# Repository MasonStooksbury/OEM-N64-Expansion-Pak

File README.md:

# OEM-N64-Expansion-Pak | KiCad 8.0

At long last! Here are the all the files you would need to create your own OEM Expansion Pak. All you would need to do is clone this repo, open the .kicad_pro file in KiCad, and you can poke around the files. [Here's a video of it working!](https://www.youtube.com/watch?v=sDxaTl5USwA)

I use this plugin in KiCad to make it super easy to order boards with all the correct settings: [https://www.pcbway.com/blog/News/PCBWay_Plug_In_for_KiCad_3ea6219c.html](https://www.pcbway.com/blog/News/PCBWay_Plug_In_for_KiCad_3ea6219c.html)

## Some things to note:

 - ***Unless you have a 4MB RAM chip, this board will not do you any good***. Most of the old stock you will find are 2MB chips. Don't fret, I have [another open source board](https://github.com/MasonStooksbury/Open-Source-N64-Expansion-Pak) that utilizes two of these chips so that you can make your own Expansion Pak. This one is just for historical reference. That being said, you can find instructions for ordering a board with the settings I use at PCBWay below in the "Making your own board" section if you happen to come across some 4MB modules, or you harvest them from a broken N64 (assuming you have the model with one 4MB chip as opposed to the ones with two 2MB chips)

 - The "ExpansionPak.pretty" folder is a library containing all the footprints needed for the project. Including the Edge Connector footprint created by Bigbass (check out more of his stuff here: [https://hachyderm.io/@bigbass](https://hachyderm.io/@bigbass) and here: [https://github.com/bigbass1997](https://github.com/bigbass1997/)). This saved me countless hours and pain, so a huge shoutout to him for allowing me to use it and release it

 - The schematic is probably not in an "official" format. But it's laid out in such a way that you can easily understand which pins on the Edge Connector are connected to which pins on the RAM chip. This was done on purpose as I feel it is a bit easier to understand for most people.

 - The pictured board and the render look different because I needed to change some things once I got the board. Namely, the corners were in the way of the original Expansion Pak mounting columns (if you look at an OEM one, they have cutouts). I also needed to modify the screw holes because they were too small.

Thank you so much to everyone who has followed along, commented, gave me feedback, and more. It's all very much appreciated and I'm excited to be able to give back. And another huge shoutout to Bigbass for allowing me to use their Edge Connector as it was a perfect fit and saved me countless revisions and lots of headache.

# Making your own board

## Installing necessary software, pulling the project, and uploading everything to PCBWay
 - First, download KiCad [here](https://www.kicad.org/download/)
 - Next, install the PCBWay plugin by following the instructions [here](https://www.pcbway.com/blog/News/PCBWay_Plug_In_for_KiCad_3ea6219c.html)
 - Clone this repository or download a ZIP of the files using the green button near the top right of the page
 - Open KiCad, then open this project by navigating to where you downloaded this repo and selecting the `.kicad_pro` file
   - 
 - Once open, click on the `.kicad_pcb` file to open up the PCB so we can begin to order it
   - 
 - From there, click the PCBWay button at the top right
   - 
 - KiCad should then automatically redirect you to a browser where it has opened up PCBWay and uploaded the necessary files so that you can begin ordering. Next we need to select all the correct options so that it will be made correctly.

## Selecting the correct options in PCBWay
 - Most of these options will be selected automatically, but be sure to set the ones in the red boxes as they are either structurally required or drastically affect cost
 - 
 - 
   - `Thickness`: This has to be 1.2 otherwise it will be too thick and you risk over-bending the receiver pins in the N64 
   - `Min hole size`: This tells PCBWay how small we need the holes for some of our vias
   - `Edge connector`: By far the most important setting. This tells PCBWay that we have what is called an `edge connector` (similar to how a RAM stick looks). That way they know to setup all the particular manufacturing stuff that is required to make these
   - `HASL lead free`: This is referring to the type of plating we want on our edge connector. Most commercial edge connectors are plated with a thin layer of hard material like gold since it can handle being seated/unseated multiple times better than most other materials. However, it's *really* expensive. I encourage you to select it just to see the price jump lol. That being said, `HASL lead free` is good enough for the Expansion Pak because you won't be removing it all that often, and even if you do, it's plenty hard enough to handle it. I pick the lead free variant cause I don't want to die early from lead poisoning
   - `Surface finish`: This is the plating that will appear on the pads where you will solder things to. `HASL lead free` is plenty good enough for this and also helps with cost
   - `Remove product No`: PCBWay adds a tracking number to the silkscreen of your boards so that their manufacturing process is a little easier. You can select the `Yes` option here and pay a little extra to have them not add that. It's not a huge deal, but something to be aware of.

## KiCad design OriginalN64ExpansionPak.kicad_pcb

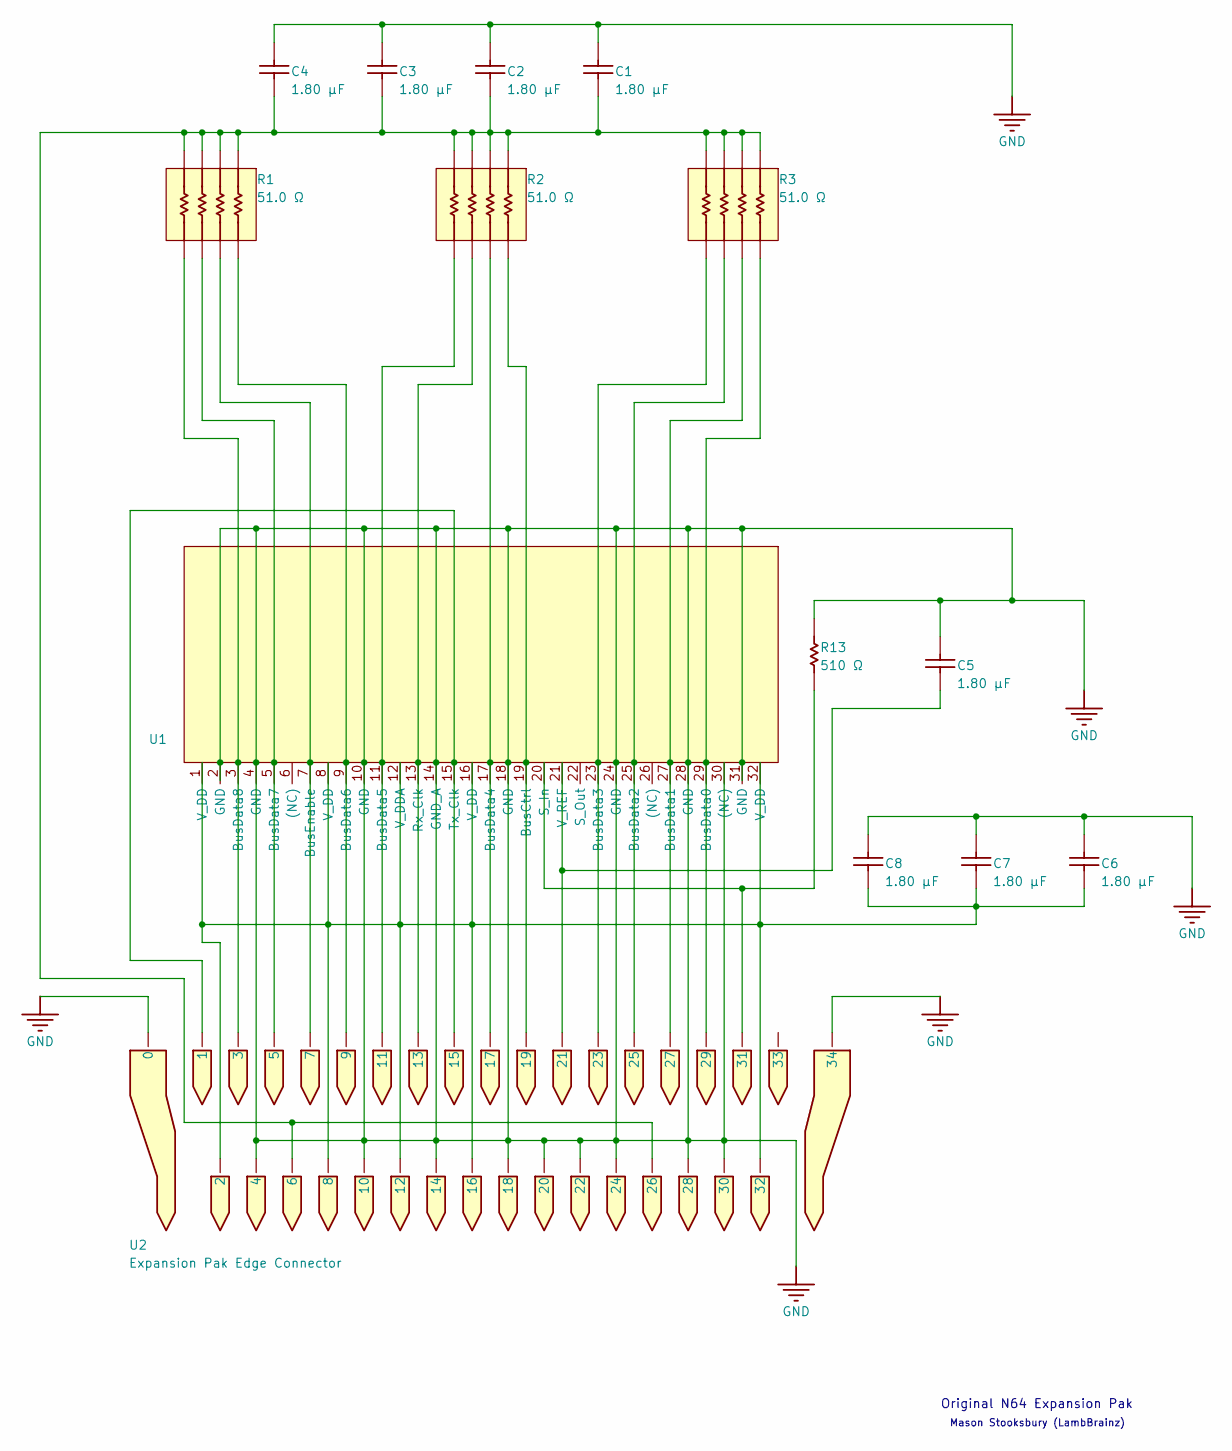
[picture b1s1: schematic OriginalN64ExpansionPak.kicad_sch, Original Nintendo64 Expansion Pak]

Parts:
C1, C2, C3, C4, C5, C6, C7, C8: KEMET C0805C185K8PAC7800; C_0805_2012Metric; CAPACITANCE TOLERANCE ±10%; VOLTAGE RATING (DC) 10.0 V; MANUFACTURER PART NUMBER C0805C185K8PAC7800
R1, R2, R3: Panasonic EXB-V8V510JV; Resistor Array; RESISTANCE TOLERANCE ±5%; MANUFACTURER PART NUMBER EXB-V8V510JV
R13: Yageo RC0805FR-07510RL; R_0805_2012Metric_Pad1.20x1.40mm_HandSolder
U1: MSM5718B70-60GS-K; RAM Module; MANUFACTURER PART NUMBER MSM5718B70-60GS-K
U2: Expansion Pak Edge Connector; EdgeConnector; PARTID 1

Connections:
GND: C1.1, C2.1, C3.1, C4.1, C5.1, C6.1, C7.1, C8.1, R13.1, U1.2 (GND), U1.4 (GND), U1.10 (GND), U1.14 (GND_A), U1.18 (GND), U1.24 (GND), U1.28 (GND), U1.30 ((NC)), U1.31 (GND), U2.0, U2.4, U2.10, U2.14, U2.18, U2.20, U2.22, U2.24, U2.28, U2.30, U2.34, U2.-
unnamed: C1.2, C2.2, C3.2, C4.2, R1.5 (2), R1.6 (2), R1.7 (2), R1.8 (2), R2.5 (2), R2.6 (2), R2.7 (2), R2.8 (2), R3.5 (2), R3.6 (2), R3.7 (2), R3.8 (2), U2.6, U2.26
unnamed: C5.2, U1.21 (V_REF), U2.21
unnamed: C6.2, C7.2, C8.2, U1.1 (V_DD), U1.8 (V_DD), U1.12 (V_DDA), U1.16 (V_DD), U1.32 (V_DD), U2.2, U2.8, U2.12, U2.16, U2.32
unnamed: R1.1, U1.3 (BusData8), U2.3
unnamed: R1.2 (1), U1.5 (BusData7), U2.5
unnamed: R1.3 (1), U1.7 (BusEnable), U2.7
unnamed: R1.4 (1), U1.9 (BusData6), U2.9
unnamed: R2.1, U1.11 (BusData5), U2.11
unnamed: R2.2 (1), U1.13 (Rx_Clk), U2.13
unnamed: R2.3 (1), U1.17 (BusData4), U2.17
unnamed: R2.4 (1), U1.19 (BusCtrl), U2.19
unnamed: R3.1, U1.23 (BusData3), U2.23
unnamed: R3.2 (1), U1.25 (BusData2), U2.25
unnamed: R3.3 (1), U1.27 (BusData1), U2.27
unnamed: R3.4 (1), U1.29 (BusData0), U2.29
unnamed: R13.2, U1.20 (S_In), U2.31
unnamed: U1.15 (Tx_Clk), U2.1, U2.15

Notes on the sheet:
Original N64 Expansion Pak
Mason Stooksbury (LambBrainz)

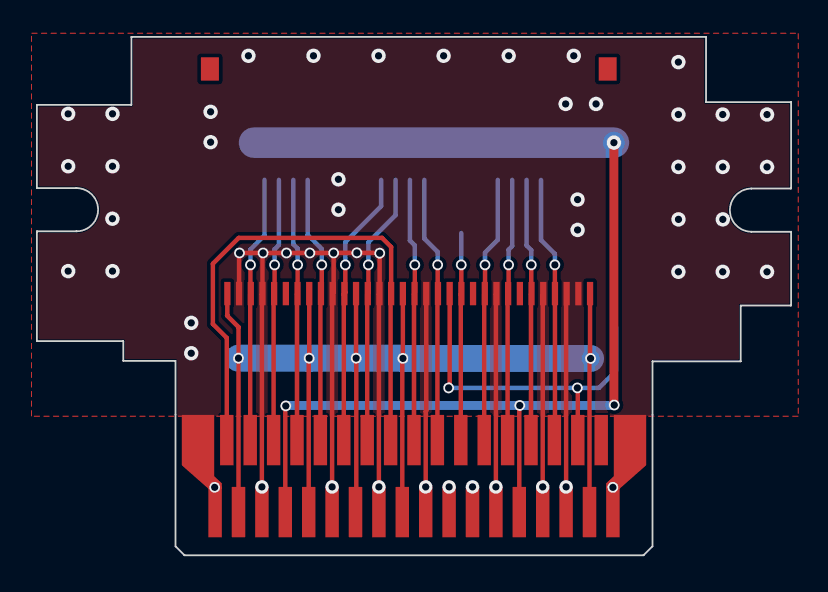
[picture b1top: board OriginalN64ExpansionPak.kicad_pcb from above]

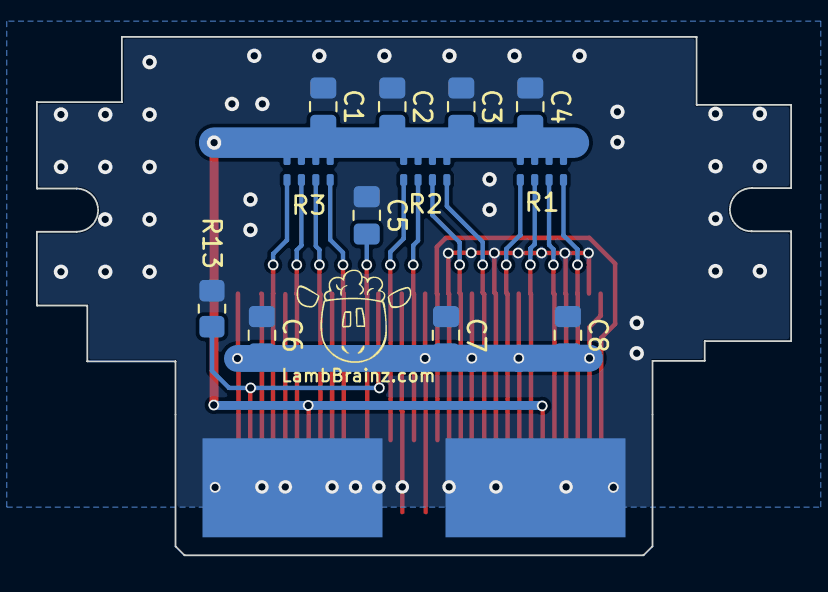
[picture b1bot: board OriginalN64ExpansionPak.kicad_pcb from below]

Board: 2 copper layers, 41.9 x 28.8 mm, 14 parts (12 on the bottom side), 18 nets.

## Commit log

2023-07-24 Updating R13 to have a larger package size so it's easier to solder by hand
2023-07-24 Adding installation/creation instructions
2023-07-24 Organizing pictures a little better
2023-07-25 Updating package size in schematic footprint
2023-07-25 Updating resistor footprint
2023-10-01 Updating solder pads to be 'Hand_Solder' variants to make soldering less painful. Also updated how the copper pours interact with the edge connector
2023-10-02 Backups
2023-12-26 Adding licenses
2024-06-28 Updating to KiCad 8.0, updating README, deleting backups

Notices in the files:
README.md:
License: CERN-OHL-P-2.0
License: MIT
